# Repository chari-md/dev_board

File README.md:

# STM32 Dev Board

This is a simple STM32 development board that I designed for my own use. It is based on the STM32F103C8T6 microcontroller. The design is inspired by the [Blue Pill][0] development board.

## Manufacturing

The board is designed to be manufactured using the [JLCPCB][1] assembly service. All the files required for manufacturing are in the `manufacturing` directory.

## Mechanical

The board is designed to be mounted in a 3D printed case. The case files are in the `case` directory or can be found on [Printables][2] and [Thingiverse][3].

The dimensions of the board are (L x W x H) 64mm x 24mm x 1.6mm.

The mounting holes are designed for [M2 ISO7380 screws][4].

[0]: https://stm32-base.org/boards/STM32F103C8T6-Blue-Pill.html
[1]: https://jlcpcb.com
[2]: https://www.thingiverse.com
[3]: https://www.printables.com
[4]: https://aliexpress.com/item/32810852732.html

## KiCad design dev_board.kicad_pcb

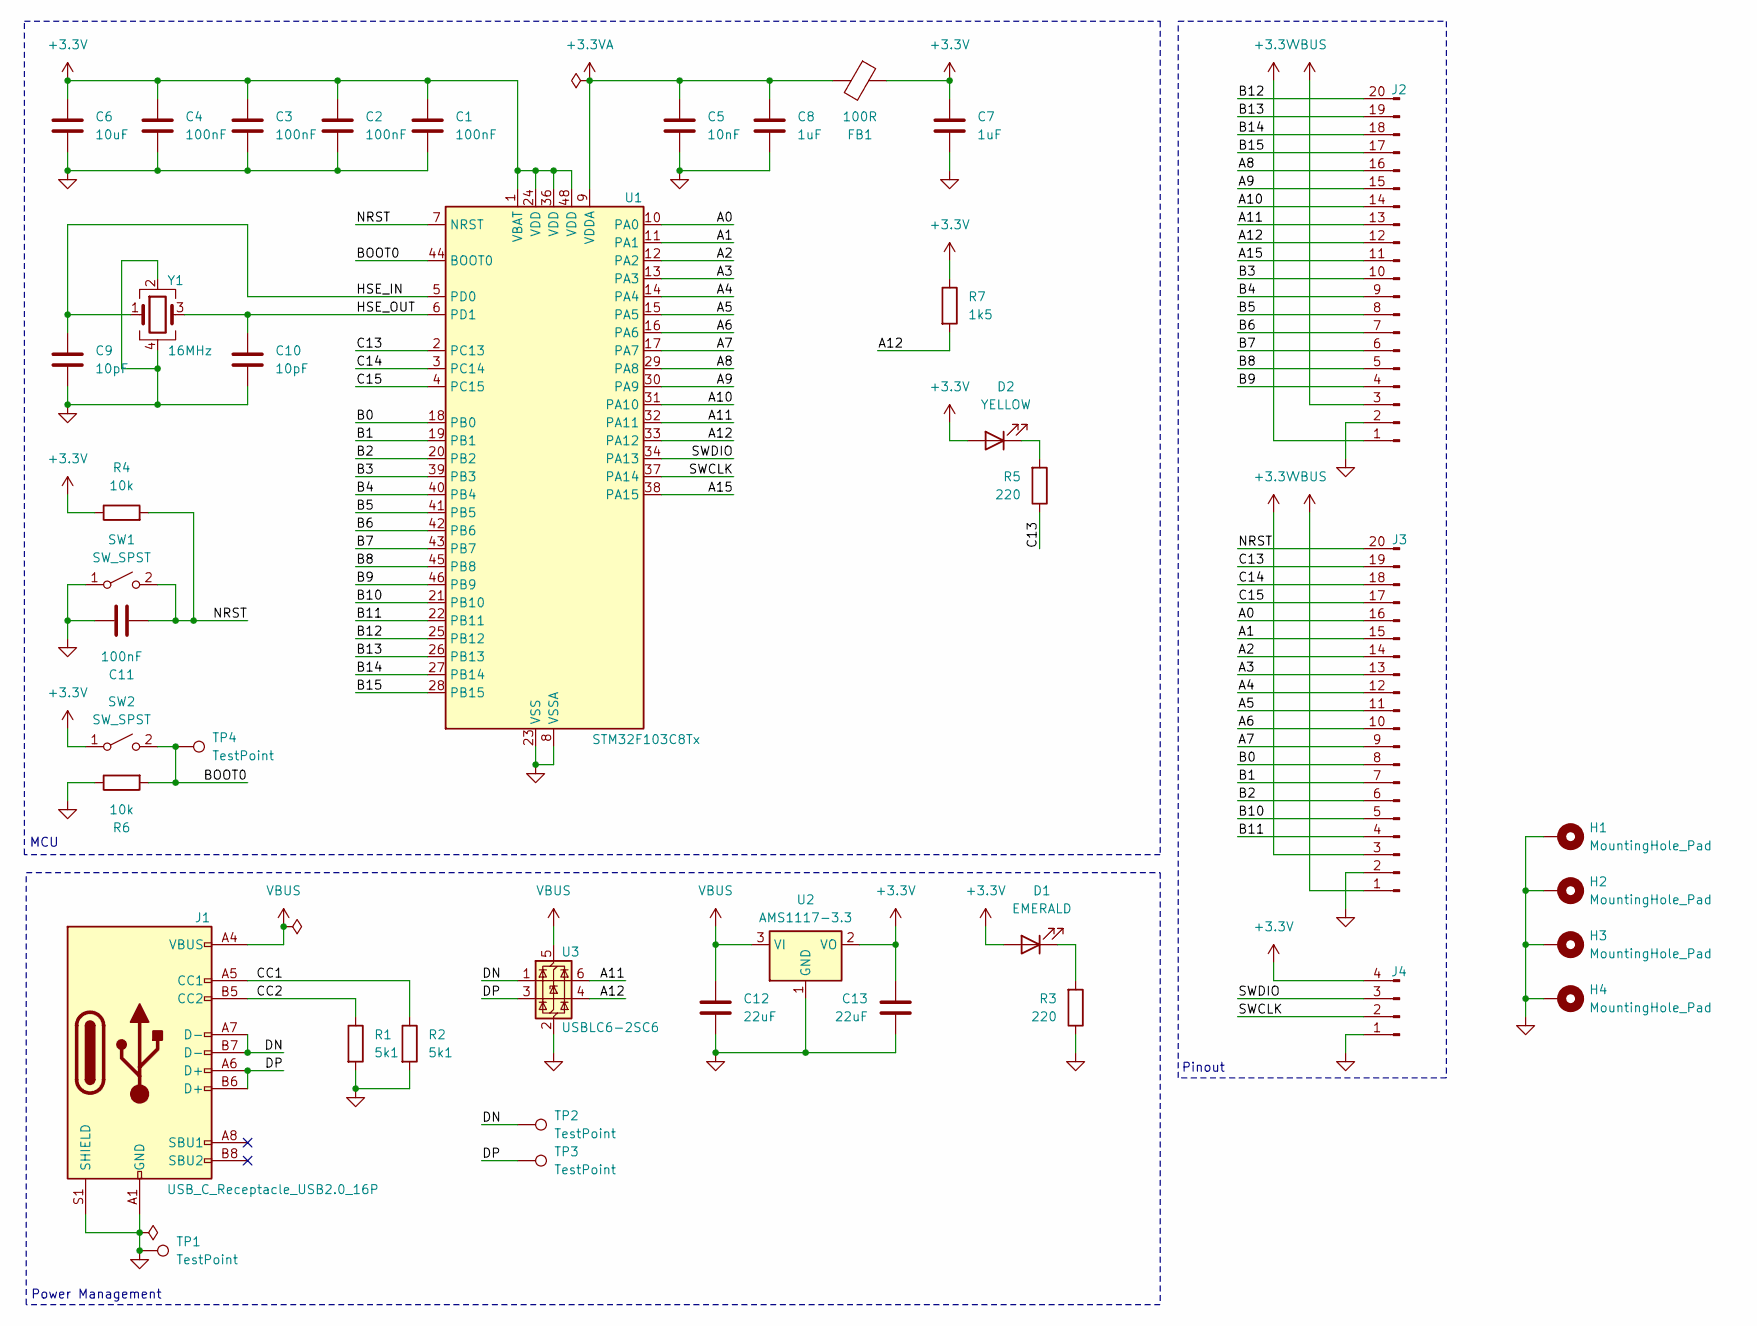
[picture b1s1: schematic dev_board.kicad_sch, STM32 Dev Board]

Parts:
C1, C2, C3, C4, C11: 100nF; C_0402_1005Metric
C5: 10nF; C_0402_1005Metric
C6: 10uF; C_0805_2012Metric
C7, C8: 1uF; C_0603_1608Metric
C9, C10: 10pF; C_0402_1005Metric
C12, C13: 22uF; C_0805_2012Metric
D1: EMERALD; LED_0805_2012Metric
D2: YELLOW; LED_0805_2012Metric
FB1: 100R; L_0805_2012Metric
H1, H2, H3, H4: MountingHole_Pad; MountingHole_2.2mm_M2_ISO7380_Pad
J1: USB_C_Receptacle_USB2.0_16P; USB_C_Receptacle_G-Switch_GT-USB-7010ASV
J2, J3: Conn_01x20_Pin; PinHeader_1x20_P2.54mm_Vertical
J4: Conn_01x04_Pin; PinHeader_1x04_P2.54mm_Vertical
R1, R2: 5k1; R_0603_1608Metric
R3, R5: 220; R_0603_1608Metric
R4, R6: 10k; R_0603_1608Metric
R7: 1k5; R_0603_1608Metric
SW1, SW2: SW_SPST; SW_Push_1P1T_XKB_TS-1187A
TP1, TP2, TP3, TP4: TestPoint; TestPoint_Pad_1.0x1.0mm
U1: STM32F103C8Tx; LQFP-48_7x7mm_P0.5mm
U2: AMS1117-3.3; SOT-223-3_TabPin2
U3: USBLC6-2SC6; SOT-23-6
Y1: 16MHz; Crystal_SMD_3225-4Pin_3.2x2.5mm

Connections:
+3.3V: C1.1, C2.1, C3.1, C4.1, C6.1, C7.1, C13.1, D1.2 (A), D2.2 (A), FB1.1, J2.1, J3.3, J4.4, R4.1, R7.1, SW2.1 (A), U1.1 (VBAT), U1.24 (VDD), U1.36 (VDD), U1.48 (VDD), U2.2 (VO)
+3.3VA: C5.1, C8.1, FB1.2, U1.9 (VDDA)
/A0: J3.16, U1.10 (PA0)
/A1: J3.15, U1.11 (PA1)
/A2: J3.14, U1.12 (PA2)
/A3: J3.13, U1.13 (PA3)
/A4: J3.12, U1.14 (PA4)
/A5: J3.11, U1.15 (PA5)
/A6: J3.10, U1.16 (PA6)
/A7: J3.9, U1.17 (PA7)
/A8: J2.16, U1.29 (PA8)
/A9: J2.15, U1.30 (PA9)
/A10: J2.14, U1.31 (PA10)
/A11: J2.13, U1.32 (PA11), U3.6 (I/O1)
/A12: J2.12, R7.2, U1.33 (PA12), U3.4 (I/O2)
/A15: J2.11, U1.38 (PA15)
/B0: J3.8, U1.18 (PB0)
/B1: J3.7, U1.19 (PB1)
/B2: J3.6, U1.20 (PB2)
/B3: J2.10, U1.39 (PB3)
/B4: J2.9, U1.40 (PB4)
/B5: J2.8, U1.41 (PB5)
/B6: J2.7, U1.42 (PB6)
/B7: J2.6, U1.43 (PB7)
/B8: J2.5, U1.45 (PB8)
/B9: J2.4, U1.46 (PB9)
/B10: J3.5, U1.21 (PB10)
/B11: J3.4, U1.22 (PB11)
/B12: J2.20, U1.25 (PB12)
/B13: J2.19, U1.26 (PB13)
/B14: J2.18, U1.27 (PB14)
/B15: J2.17, U1.28 (PB15)
/BOOT0: R6.2, SW2.2 (B), TP4.1, U1.44 (BOOT0)
/C13: J3.19, R5.1, U1.2 (PC13)
/C14: J3.18, U1.3 (PC14)
/C15: J3.17, U1.4 (PC15)
/CC1: J1.A5 (CC1), R2.1
/CC2: J1.B5 (CC2), R1.1
/DN: J1.A7 (D-), J1.B7 (D-), TP2.1, U3.1 (I/O1)
/DP: J1.A6 (D+), J1.B6 (D+), TP3.1, U3.3 (I/O2)
/HSE_IN: C9.1, U1.5 (PD0), Y1.1
/HSE_OUT: C10.1, U1.6 (PD1), Y1.3
/NRST: C11.1, J3.20, R4.2, SW1.2 (B), U1.7 (NRST)
/SWCLK: J4.2, U1.37 (PA14)
/SWDIO: J4.3, U1.34 (PA13)
GND: C1.2, C2.2, C3.2, C4.2, C5.2, C6.2, C7.2, C8.2, C9.2, C10.2, C11.2, C12.2, C13.2, H1.1, H2.1, H3.1, H4.1, J1.A1 (GND), J1.A12 (GND), J1.B1 (GND), J1.B12 (GND), J1.S1 (SHIELD), J2.2, J3.2, J4.1, R1.2, R2.2, R3.1, R6.1, SW1.1 (A), TP1.1, U1.8 (VSSA), U1.23 (VSS), U1.35 (VSS), U1.47 (VSS), U2.1 (GND), U3.2 (GND), Y1.2, Y1.4
unnamed: D1.1 (K), R3.2
unnamed: D2.1 (K), R5.2
VBUS: C12.1, J1.A4 (VBUS), J1.A9 (VBUS), J1.B4 (VBUS), J1.B9 (VBUS), J2.3, J3.1, U2.3 (VI), U3.5 (VBUS)

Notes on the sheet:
Pinout
Power Management
MCU

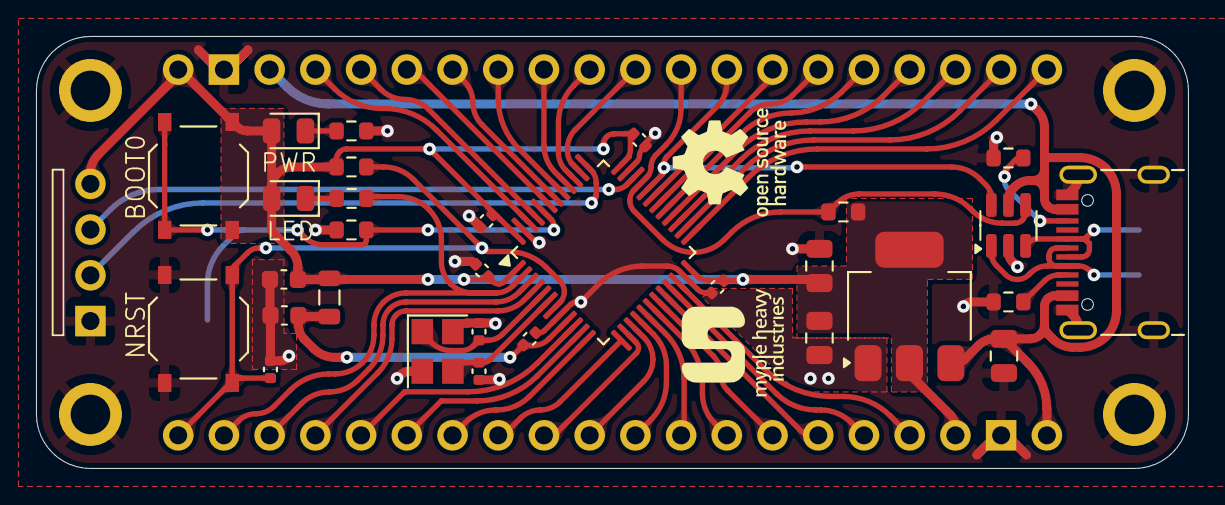
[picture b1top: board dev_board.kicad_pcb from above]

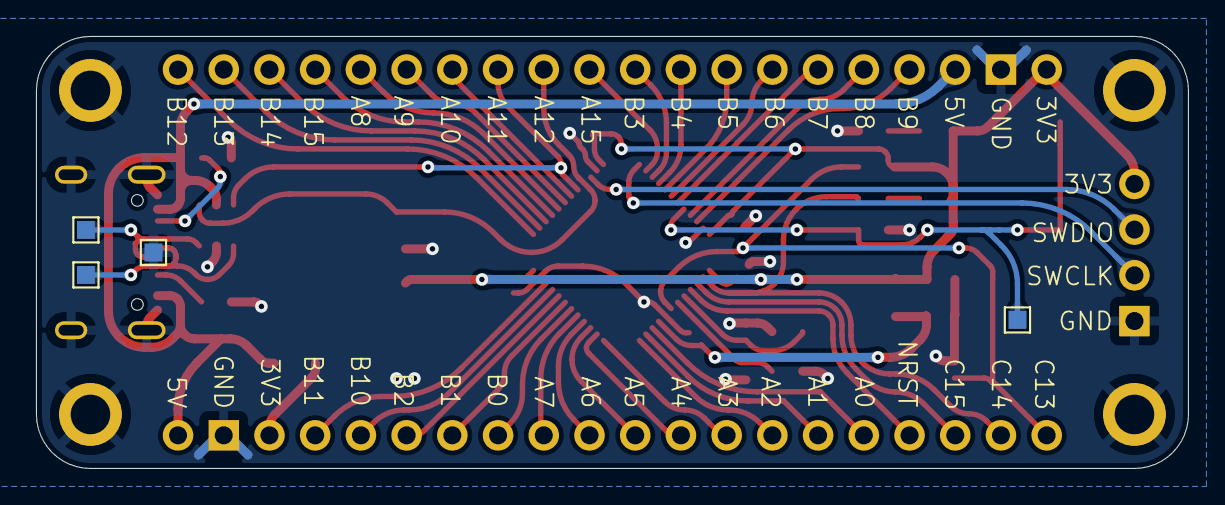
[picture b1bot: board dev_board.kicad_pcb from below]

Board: 2 copper layers, 64.0 x 24.0 mm, 41 parts (4 on the bottom side), 49 nets.

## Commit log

2024-07-01 init commit
2024-07-03 opt: zone fills and remove some vias after feedback
2024-08-16 feat: add tear drops
2024-08-16 feat: round tracks
2024-08-16 chore: update image
